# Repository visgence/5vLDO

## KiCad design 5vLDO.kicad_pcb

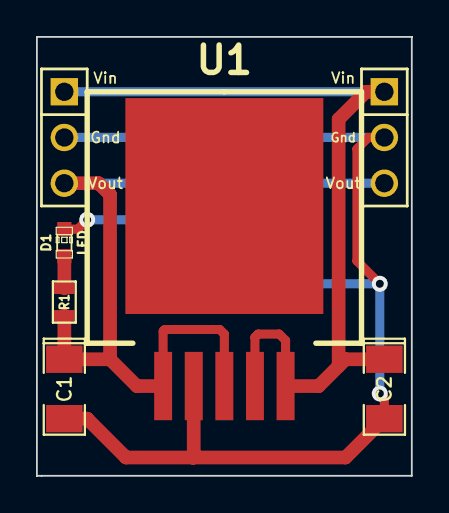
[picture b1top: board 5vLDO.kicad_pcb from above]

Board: 2 copper layers, 20.8 x 24.4 mm, 7 parts (0 on the bottom side), 4 nets.

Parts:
C1, C2: CP1; SM1206POL
D1: LED; LED-0603
K1, K2: CONN_3; PIN_ARRAY_3X1
R1: R; SM0603
U1: AP1186K5; TO-263-5

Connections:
GND: C1.2, C2.2, D1.2, K1.2, K2.2, U1.2
unnamed: D1.1, R1.2
Vin: C2.1, K1.1, K2.1, U1.4, U1.5
Vout: C1.1, K1.3, K2.3, R1.1, U1.1, U1.3

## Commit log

2013-09-18 Added first attempt of 5vLDO breakout
2013-09-18 unknown save
2013-09-21 Added edge, fixed missing trace
